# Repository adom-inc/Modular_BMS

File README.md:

# Modular BMS Repository

This repository contains hardware and firmware for a **Modular Battery Management System (BMS)**.

## Notes

To reset the system, please power cycle the MSP Ez-FET Lite Molecule which powers the MSP onboard the BQ76952EVM. 
If for some reason the BQ76952 chip itself is stuck, you may pull the "RST_SHUT" line high (or to REG1)
A minimum of 3 batteries are required

## Firmware Documentation
Detailed firmware documentation can be found in:

```
Modular_BMS/PlatformIO/MSP430_BQ76952/src/README.md
```

This README covers firmware architecture, configuration, and usage for the MSP430 + BQ76952 system.

## PlatformIO Setup
Instructions for setting up the PlatformIO development environment are located in:

```
Modular_BMS/PlatformIO/README.md
```

Please follow that guide before attempting to build or flash the firmware.

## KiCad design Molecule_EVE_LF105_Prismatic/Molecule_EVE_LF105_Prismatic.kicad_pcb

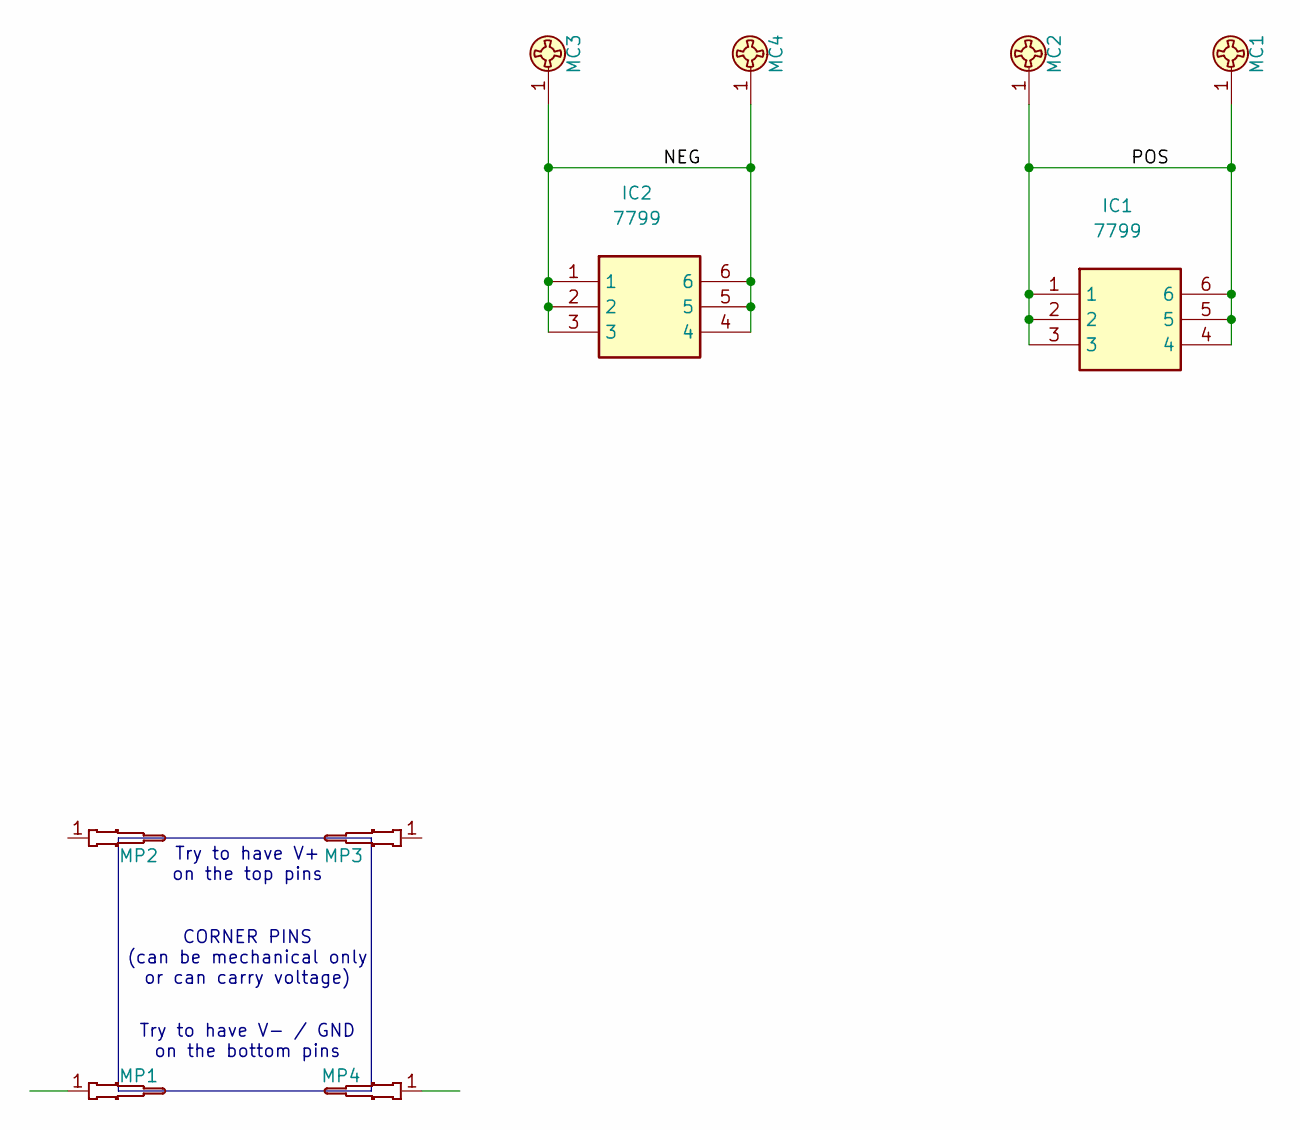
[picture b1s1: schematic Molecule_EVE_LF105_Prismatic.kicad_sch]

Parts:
IC1, IC2: 7799; Mouser Part Number 534-7799
MC1, MC2, MC3, MC4: ADOM_LARGE_CONTACT_v2
MP1, MP2, MP3, MP4: ADOM_LARGE_PIN_v3_PRESS_FIT

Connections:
/NEG: IC2.1, IC2.2, IC2.3, IC2.4, IC2.5, IC2.6, MC3.1, MC4.1
/POS: IC1.1, IC1.2, IC1.3, IC1.4, IC1.5, IC1.6, MC1.1, MC2.1

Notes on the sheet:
Try to have V+ on the top pins
CORNER PINS (can be mechanical only or can carry voltage)
Try to have V- / GND on the bottom pins

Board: 2 copper layers, 10 parts (0 on the bottom side), 2 nets, no tracks yet.

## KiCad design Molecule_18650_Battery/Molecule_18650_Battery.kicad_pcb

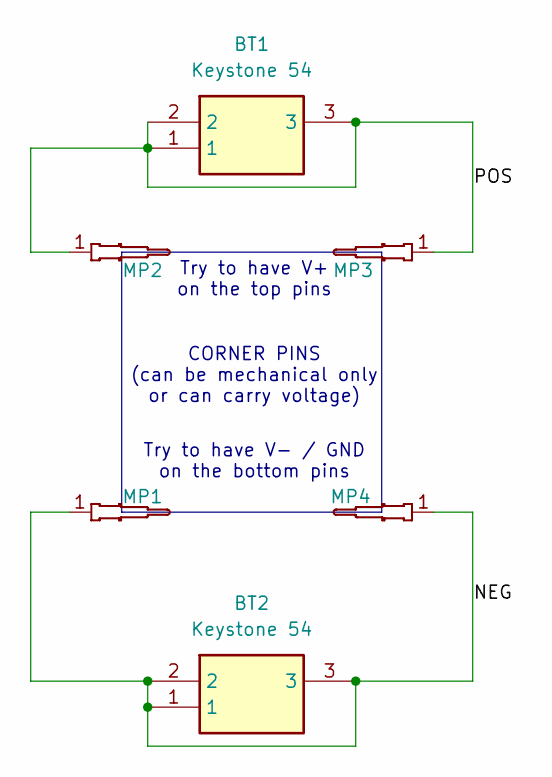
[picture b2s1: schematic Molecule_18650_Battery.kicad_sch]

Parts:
BT1, BT2: Keystone 54; Mouser Part Number 534-54
MP1, MP2, MP3, MP4: ADOM_MEDIUM_PIN_SHORTER_v1

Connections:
/NEG: BT2.1, BT2.2, BT2.3, MP1.1, MP4.1
/POS: BT1.1, BT1.2, BT1.3, MP2.1, MP3.1

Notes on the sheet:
Try to have V+ on the top pins
CORNER PINS (can be mechanical only or can carry voltage)
Try to have V- / GND on the bottom pins

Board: 2 copper layers, 6 parts (0 on the bottom side), 2 nets, no tracks yet.

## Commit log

2025-10-29 Almost finished board. Working on BOM/POS
2025-10-29 uploaded 18650 carrier/jumper
2025-11-07 Final production
    Updated sizing and bug fixes
2025-12-12 BMS firmware V1 complete
2025-12-15 Added prismatic cell
